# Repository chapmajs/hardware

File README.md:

Open Source Hardware Projects
=============================

This repository contains projects released as [Open Source Hardware (OSHW)](http://www.openhardware.org/). All works contained within this repository are covered by a [Creative Commons Attribution-ShareAlike 3.0 license (CC BY-SA 3.0)](http://creativecommons.org/licenses/by-sa/3.0/).

EAGLE Libraries
---------------

Project subdirectory `eagle_libs` contains custom parts libraries for CADSoft EAGLE used in projects hosted in this repository. Individual project READMEs may link to other parts libraries that are not part of the current EAGLE base distribution.

Projects are broken down into subfolders containing the layout and schematic for the project and an individual README.

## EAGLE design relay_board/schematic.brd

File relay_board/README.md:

24V Isolated Relay Controller
=============================

An OSHW combined power supply and current loop controller for 24V relays. The writeup for this project can be found [here](http://www.glitchwrks.com/2013/02/28/Relay-Board/)

This project is released as [Open Source Hardware (OSHW)](http://www.openhardware.org/). All works contained within this repository are covered by a [Creative Commons Attribution-ShareAlike 3.0 license (CC BY-SA 3.0)](http://creativecommons.org/licenses/by-sa/3.0/)

External Libraries
------------------

This project requires the Glitchworks library from [https://github.com/chapmajs/hardware/eagle_libs](https://github.com/chapmajs/hardware/eagle_libs) as well as the OSHW logo file from [oshwlogo.com](http://www.oshwlogo.com) (found [here](http://oshwlogo.com/logos/ohw-logo.lbr)).

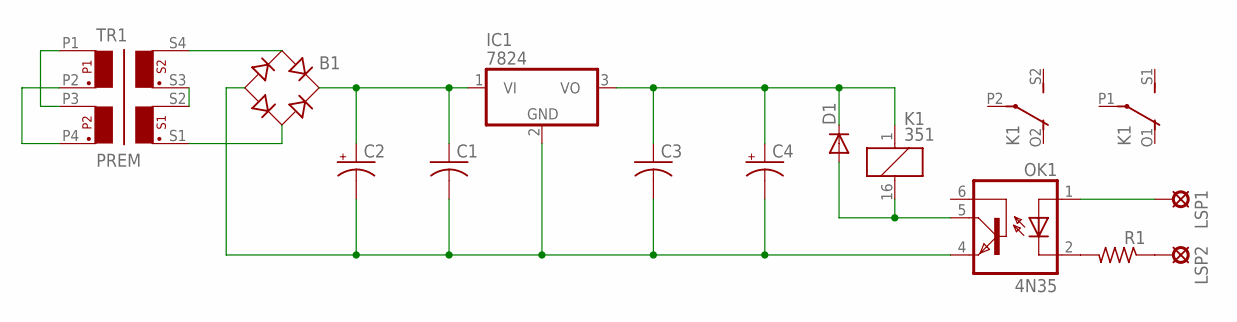
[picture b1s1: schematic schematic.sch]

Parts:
B1: B-DIL
C1, C3: C-US025-024X044; C025-024X044
C2: CPOL-USE5-8.5; E5-8,5
C4: CPOL-USE2.5-7; E2,5-7
D1: 1N4148DO35-7; DO35-7
IC1: 7824; TO220H
K1: 351
LSP1, LSP2: LSP10
OK1: 4N35; DIL06
R1: R-US_0204/2V; 0204V
TR1: PREM; PREM-2P2S

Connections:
unnamed: TR1.S2, TR1.S3
unnamed: B1.AC1, TR1.S4
unnamed: B1.AC2, TR1.S1
unnamed: B1.+, C1.1, C2.+, IC1.1 (VI)
unnamed: B1.-, C1.2, C2.-, C3.2, C4.-, IC1.2 (GND), OK1.4 (EMI)
unnamed: C3.1, C4.+, D1.C, IC1.3 (VO), K1.1
unnamed: D1.A, K1.16 (2), OK1.5 (COL)
unnamed: OK1.2 (C), R1.2
unnamed: LSP1.MP, OK1.1 (A)
unnamed: LSP2.MP, R1.1
unnamed: TR1.P1, TR1.P3
unnamed: TR1.P2, TR1.P4

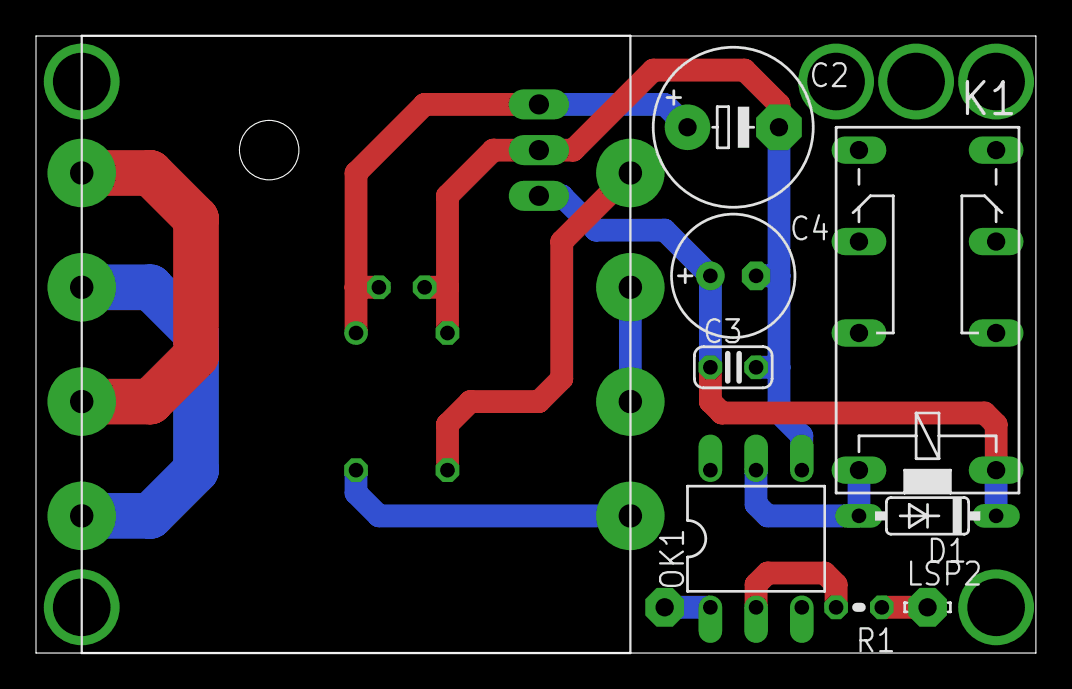
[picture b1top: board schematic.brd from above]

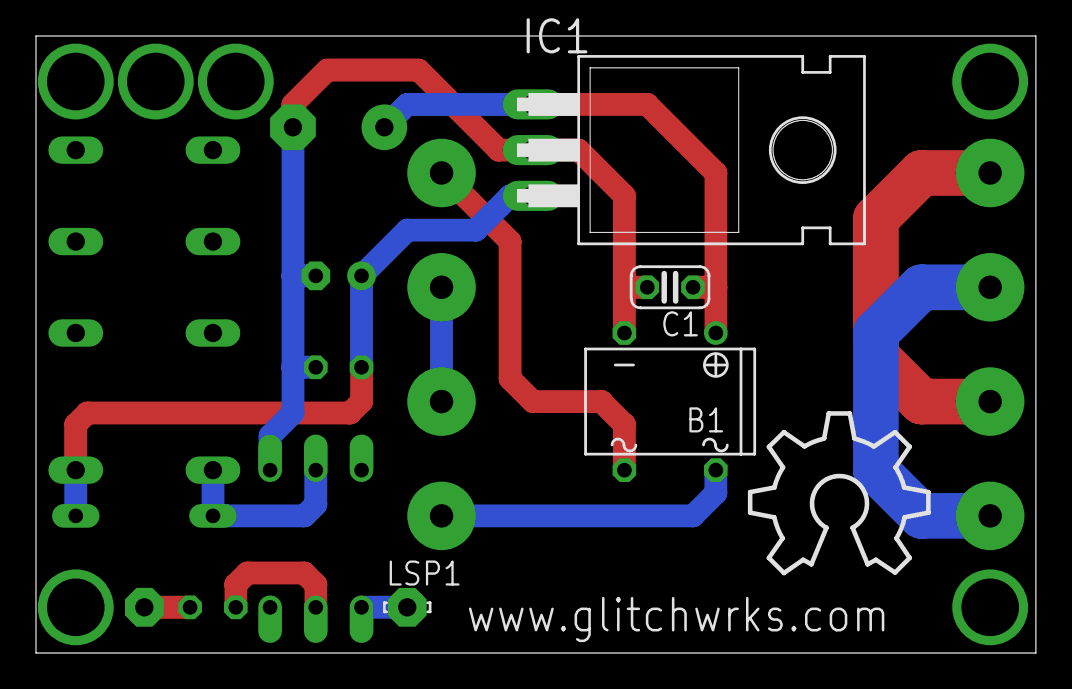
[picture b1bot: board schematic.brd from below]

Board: 2 copper layers, 55.5 x 34.3 mm, 14 parts (5 on the bottom side), 12 nets.

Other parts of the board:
U$1: OSHW_10X350_NOTEXT

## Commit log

2013-03-04 Initial project README
2013-03-04 Adding Glitchworks EAGLE lib
2013-03-04 Adding relay module board/schematic/README
2013-03-04 Adding license note
2013-03-04 Adding link to project writeup
